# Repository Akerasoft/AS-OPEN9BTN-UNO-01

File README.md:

# AS-OPEN9BTN-UNOSHLD-01
An implementation of an NES Classic controller with a home button as an Arduino Shield

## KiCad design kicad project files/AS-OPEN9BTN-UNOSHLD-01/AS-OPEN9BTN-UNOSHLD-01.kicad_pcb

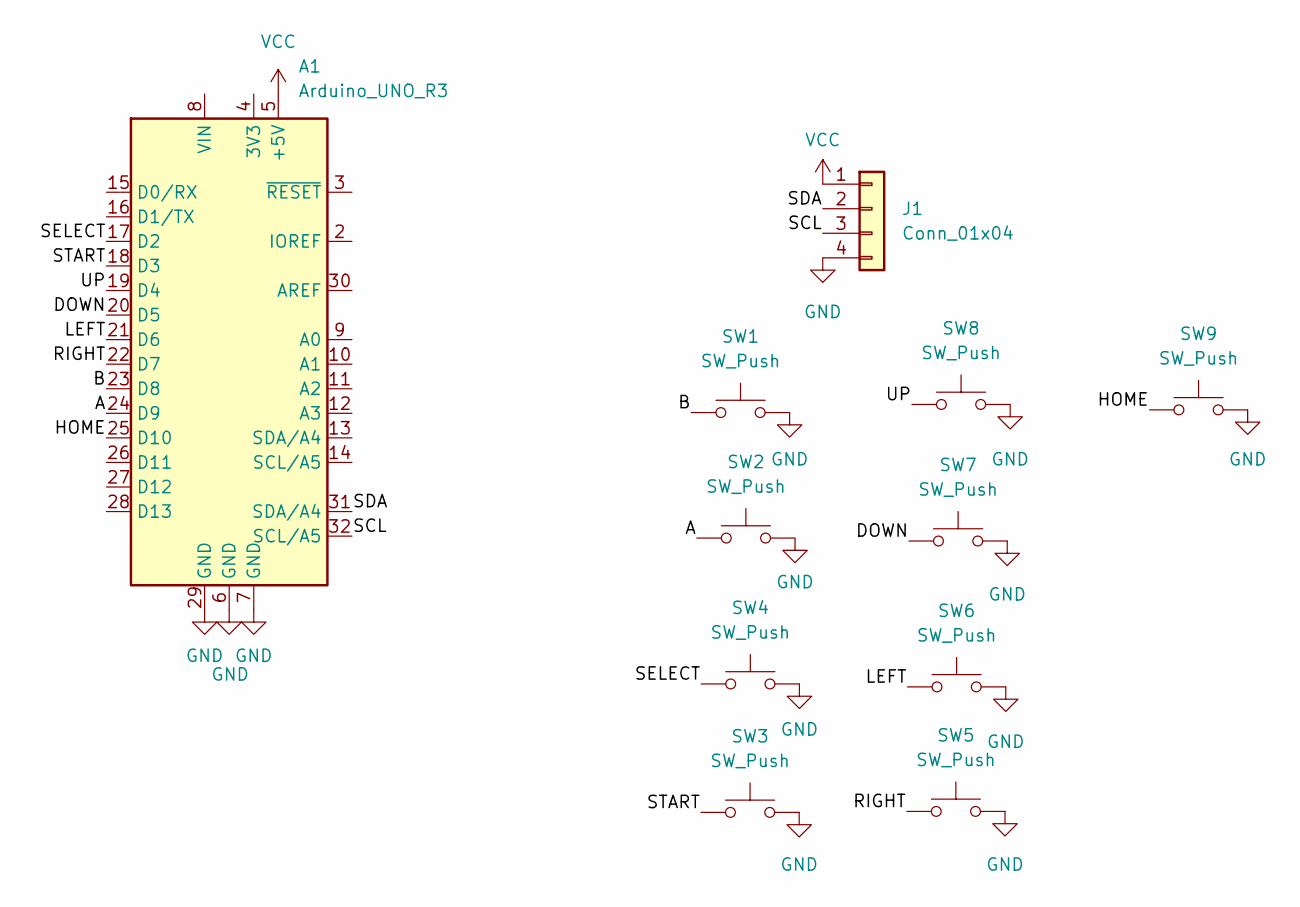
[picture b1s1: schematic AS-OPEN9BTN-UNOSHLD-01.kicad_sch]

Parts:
A1: Arduino_UNO_R3
J1: Conn_01x04
SW1, SW2, SW3, SW4, SW5, SW6, SW7, SW8, SW9: SW_Push; SW_PUSH_6mm_H4.3mm

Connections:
/A: A1.24 (D9), SW2.1
/B: A1.23 (D8), SW1.1
/DOWN: A1.20 (D5), SW7.1
/HOME: A1.25 (D10), SW9.1
/LEFT: A1.21 (D6), SW6.1
/RIGHT: A1.22 (D7), SW5.1
/SCL: A1.32 (SCL/A5), J1.3
/SDA: A1.31 (SDA/A4), J1.2
/SELECT: A1.17 (D2), SW4.1
/START: A1.18 (D3), SW3.1
/UP: A1.19 (D4), SW8.1
GND: A1.6 (GND), A1.7 (GND), A1.29 (GND), J1.4, SW1.2, SW2.2, SW3.2, SW4.2, SW5.2, SW6.2, SW7.2, SW8.2, SW9.2
VCC: A1.5 (+5V), J1.1

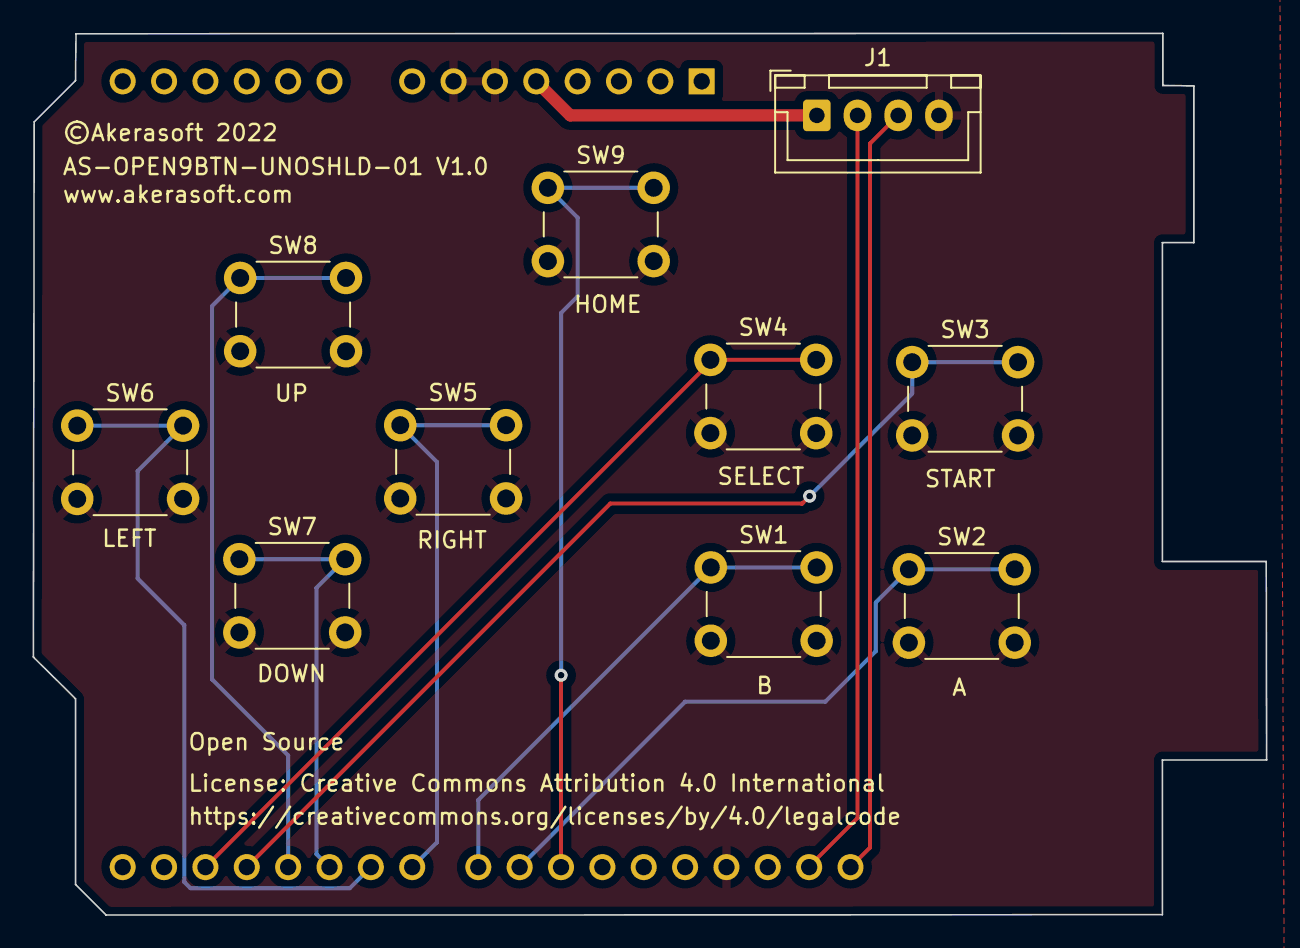
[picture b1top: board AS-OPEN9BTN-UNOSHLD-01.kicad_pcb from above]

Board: 2 copper layers, 75.7 x 54.2 mm, 11 parts (1 on the bottom side), 13 nets.

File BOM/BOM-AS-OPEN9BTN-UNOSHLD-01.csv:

Id,Designator,Package,Quantity,Part Number,Manufacturer,Alternative
1,"SW1,SW2,SW3,SW4,SW5,SW6,SW7,SW8,SW9",SW_PUSH_6mm_H4.3mm,9,1977120-2,TE Connectivity ALCOSWITCH Switches,"Taiss, Part KG-1, Amazon ASIN B0796QL57S"
2,J1,JST_XH_B4B-XH-A_1x04_P2.50mm_Vertical,1,JST XH-A B4B,JST,
3,P1,01x06 pin header - CONN HEADER VERT 6POS 2.54MM,1,61300611121,Würth Elektronik,
4,"P2,P3",01x08 pin header - CONN HEADER VERT 8POS 2.54MM,2,61300811121,Würth Elektronik,
5,P4,01x10 pin header - CONN HEADER VERT 10POS 2.54MM,1,PH1-10-UA,Adam Tech,

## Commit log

2022-11-27 First PCB commit
2022-11-27 Updated files and made 3D models
2022-11-27 BOM and Gerber prep
2022-11-27 First step to voltage convertion
2022-11-28 Used smaller chip for logic level conversion

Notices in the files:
kicad project files/AS-OPEN9BTN-UNOSHLD-01/AS-OPEN9BTN-UNOSHLD-01.kicad_pcb:
©Akerasoft 2022
License: Creative Commons Attribution 4.0 International
https://creativecommons.org/licenses/by/4.0/legalcode
